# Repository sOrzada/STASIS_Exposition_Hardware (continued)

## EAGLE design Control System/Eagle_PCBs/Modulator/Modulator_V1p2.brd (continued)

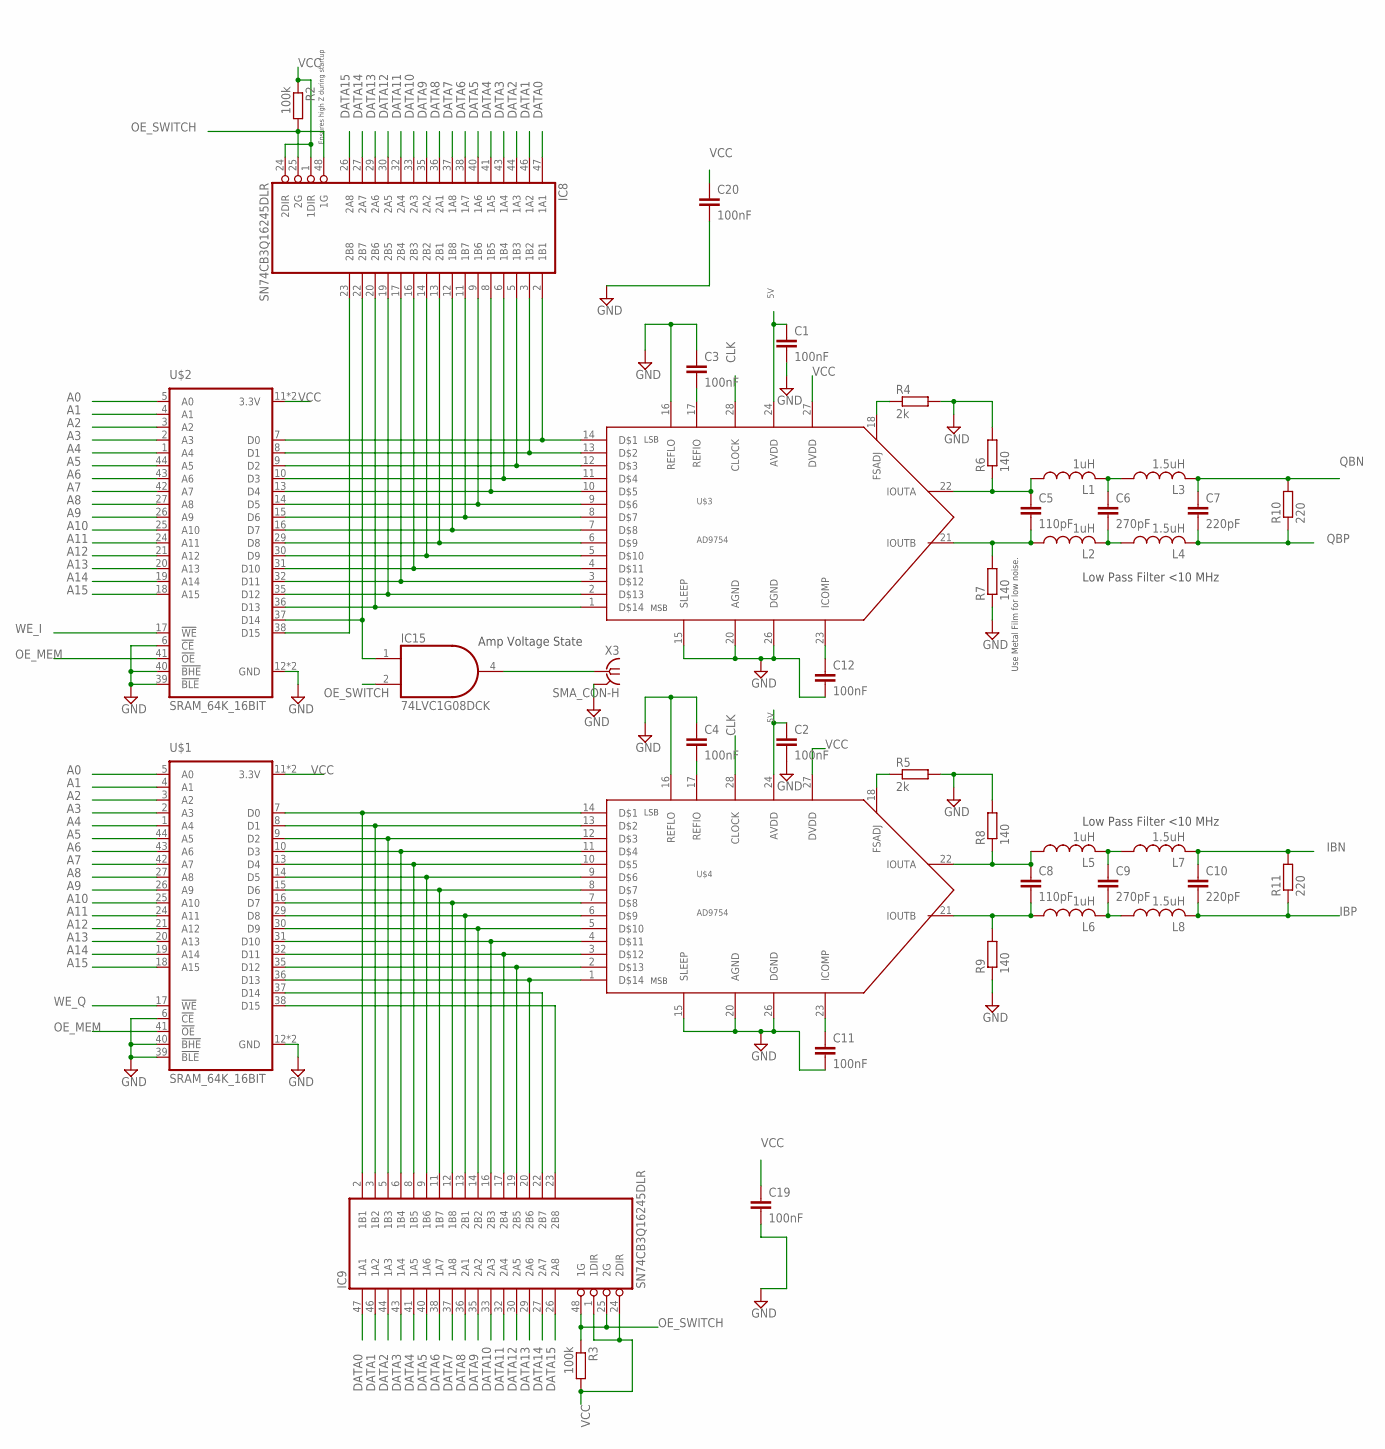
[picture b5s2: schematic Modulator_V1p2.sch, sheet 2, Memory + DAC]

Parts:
C1, C2, C3, C4, C11, C12, C19, C20: 100nF; C0603
C5, C8: 110pF; C0603
C6, C9: 270pF; C0603
C7, C10: 220pF; C0603
IC8, IC9: SN74CB3Q16245DLR; SSOP48DL
IC15: 74LVC1G08DCK; SC70-5
L1, L2, L5, L6: 1uH; L2012C
L3, L4, L7, L8: 1.5uH; L2012C
R2, R3: 100k; R0603
R4, R5: 2k; R0603
R6, R7, R8, R9: 140; R0603
R10, R11: 220; R0603
U$1, U$2: SRAM_64K_16BIT; TSOPII-Z44
U$3, U$4: AD9754; TSSOP28
X3: SMA_CON-H; BU-SMA-H

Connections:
5V: C1.1, C2.1, U$3.24 (AVDD), U$4.24 (AVDD); also elsewhere on the board
A0: U$1.5 (A0), U$2.5 (A0); also elsewhere on the board
A1: U$1.4 (A1), U$2.4 (A1); also elsewhere on the board
A2: U$1.3 (A2), U$2.3 (A2); also elsewhere on the board
A3: U$1.2 (A3), U$2.2 (A3); also elsewhere on the board
A4: U$1.1 (A4), U$2.1 (A4); also elsewhere on the board
A5: U$1.44 (A5), U$2.44 (A5); also elsewhere on the board
A6: U$1.43 (A6), U$2.43 (A6); also elsewhere on the board
A7: U$1.42 (A7), U$2.42 (A7); also elsewhere on the board
A8: U$1.27 (A8), U$2.27 (A8); also elsewhere on the board
A9: U$1.26 (A9), U$2.26 (A9); also elsewhere on the board
A10: U$1.25 (A10), U$2.25 (A10); also elsewhere on the board
A11: U$1.24 (A11), U$2.24 (A11); also elsewhere on the board
A12: U$1.21 (A12), U$2.21 (A12); also elsewhere on the board
A13: U$1.20 (A13), U$2.20 (A13); also elsewhere on the board
A14: U$1.19 (A14), U$2.19 (A14); also elsewhere on the board
A15: U$1.18 (A15), U$2.18 (A15); also elsewhere on the board
CLK: U$3.28 (CLOCK), U$4.28 (CLOCK); also elsewhere on the board
DATA0: IC8.47 (1A1), IC9.47 (1A1); also elsewhere on the board
DATA1: IC8.46 (1A2), IC9.46 (1A2); also elsewhere on the board
DATA2: IC8.44 (1A3), IC9.44 (1A3); also elsewhere on the board
DATA3: IC8.43 (1A4), IC9.43 (1A4); also elsewhere on the board
DATA4: IC8.41 (1A5), IC9.41 (1A5); also elsewhere on the board
DATA5: IC8.40 (1A6), IC9.40 (1A6); also elsewhere on the board
DATA6: IC8.38 (1A7), IC9.38 (1A7); also elsewhere on the board
DATA7: IC8.37 (1A8), IC9.37 (1A8); also elsewhere on the board
DATA8: IC8.36 (2A1), IC9.36 (2A1); also elsewhere on the board
DATA9: IC8.35 (2A2), IC9.35 (2A2); also elsewhere on the board
DATA10: IC8.33 (2A3), IC9.33 (2A3); also elsewhere on the board
DATA11: IC8.32 (2A4), IC9.32 (2A4); also elsewhere on the board
DATA12: IC8.30 (2A5), IC9.30 (2A5); also elsewhere on the board
DATA13: IC8.29 (2A6), IC9.29 (2A6); also elsewhere on the board
DATA14: IC8.27 (2A7), IC9.27 (2A7); also elsewhere on the board
DATA15: IC8.26 (2A8), IC9.26 (2A8); also elsewhere on the board
DI0: IC8.2 (1B1), U$2.7 (D0), U$3.14
DI1: IC8.3 (1B2), U$2.8 (D1), U$3.13
DI2: IC8.5 (1B3), U$2.9 (D2), U$3.12
DI3: IC8.6 (1B4), U$2.10 (D3), U$3.11
DI4: IC8.8 (1B5), U$2.13 (D4), U$3.10
DI5: IC8.9 (1B6), U$2.14 (D5), U$3.9
DI6: IC8.11 (1B7), U$2.15 (D6), U$3.8
DI7: IC8.12 (1B8), U$2.16 (D7), U$3.7
DI8: IC8.13 (2B1), U$2.29 (D8), U$3.6
DI9: IC8.14 (2B2), U$2.30 (D9), U$3.5
DI10: IC8.16 (2B3), U$2.31 (D10), U$3.4
DI11: IC8.17 (2B4), U$2.32 (D11), U$3.3
DI12: IC8.19 (2B5), U$2.35 (D12), U$3.2
DI13: IC8.20 (2B6), U$2.36 (D13), U$3.1
DQ0: IC9.2 (1B1), U$1.7 (D0), U$4.14
DQ1: IC9.3 (1B2), U$1.8 (D1), U$4.13
DQ2: IC9.5 (1B3), U$1.9 (D2), U$4.12
DQ3: IC9.6 (1B4), U$1.10 (D3), U$4.11
DQ4: IC9.8 (1B5), U$1.13 (D4), U$4.10
DQ5: IC9.9 (1B6), U$1.14 (D5), U$4.9
DQ6: IC9.11 (1B7), U$1.15 (D6), U$4.8
DQ7: IC9.12 (1B8), U$1.16 (D7), U$4.7
DQ8: IC9.13 (2B1), U$1.29 (D8), U$4.6
DQ9: IC9.14 (2B2), U$1.30 (D9), U$4.5
DQ10: IC9.16 (2B3), U$1.31 (D10), U$4.4
DQ11: IC9.17 (2B4), U$1.32 (D11), U$4.3
DQ12: IC9.19 (2B5), U$1.35 (D12), U$4.2
DQ13: IC9.20 (2B6), U$1.36 (D13), U$4.1
GND: C1.2, C2.2, C3.1, C4.1, C11.2, C12.2, C19.2, C20.2, IC8.4 (GND), IC8.10 (GND), IC8.15 (GND), IC8.21 (GND), IC8.28 (GND), IC8.34 (GND), IC8.39 (GND), IC8.45 (GND), IC9.4 (GND), IC9.10 (GND), IC9.15 (GND), IC9.21 (GND), IC9.28 (GND), IC9.34 (GND), IC9.39 (GND), IC9.45 (GND), IC15.3 (GND), R4.2, R5.2, R6.2, R7.1, R8.2, R9.1, U$1.6 (!CE), U$1.12 (GND), U$1.34 (GND), U$1.39 (!BLE), U$1.40 (!BHE), U$2.6 (!CE), U$2.12 (GND), U$2.34 (GND), U$2.39 (!BLE), U$2.40 (!BHE), U$3.15 (SLEEP), U$3.16 (REFLO), U$3.20 (AGND), U$3.26 (DGND), U$4.15 (SLEEP), U$4.16 (REFLO), U$4.20 (AGND), U$4.26 (DGND), X3.2 (GND), X3.3 (GND), X3.4 (GND), X3.5 (GND); also elsewhere on the board
IBN: C10.1, L7.2, R11.2; also elsewhere on the board
IBP: C10.2, L8.2, R11.1; also elsewhere on the board
unnamed: IC8.22 (2B7), IC15.1 (I0), U$2.37 (D14)
unnamed: IC8.23 (2B8), U$2.38 (D15)
unnamed: IC9.22 (2B7), U$1.37 (D14)
unnamed: IC9.23 (2B8), U$1.38 (D15)
unnamed: R5.1, U$4.18 (FSADJ)
unnamed: IC15.4 (O), X3.1
unnamed: C6.1, L1.2, L3.1
unnamed: R4.1, U$3.18 (FSADJ)
unnamed: C6.2, L2.2, L4.1
unnamed: C3.2, U$3.17 (REFIO)
unnamed: C4.2, U$4.17 (REFIO)
unnamed: C8.1, L5.1, R8.1, U$4.22 (IOUTA)
unnamed: C8.2, L6.1, R9.2, U$4.21 (IOUTB)
unnamed: C5.1, L1.1, R6.1, U$3.22 (IOUTA)
unnamed: C9.1, L5.2, L7.1
unnamed: C5.2, L2.1, R7.2, U$3.21 (IOUTB)
unnamed: C11.1, U$4.23 (ICOMP)
unnamed: C9.2, L6.2, L8.1
unnamed: C12.1, U$3.23 (ICOMP)
OE_MEM: U$1.41 (!OE), U$2.41 (!OE); also elsewhere on the board
OE_SWITCH: IC8.25 (2G), IC8.48 (1G), IC9.25 (2G), IC9.48 (1G), IC15.2 (I1), R2.2, R3.1; also elsewhere on the board
QBN: C7.1, L3.2, R10.2; also elsewhere on the board
QBP: C7.2, L4.2, R10.1; also elsewhere on the board
VCC: C19.1, C20.1, IC8.1 (1DIR), IC8.7 (VCC), IC8.18 (VCC), IC8.24 (2DIR), IC8.31 (VCC), IC8.42 (VCC), IC9.1 (1DIR), IC9.7 (VCC), IC9.18 (VCC), IC9.24 (2DIR), IC9.31 (VCC), IC9.42 (VCC), IC15.5 (VCC), R2.1, R3.2, U$1.11 (3.3V), U$1.33 (3.3V), U$2.11 (3.3V), U$2.33 (3.3V), U$3.27 (DVDD), U$4.27 (DVDD); also elsewhere on the board
WE_I: U$2.17 (!WE); also elsewhere on the board
WE_Q: U$1.17 (!WE); also elsewhere on the board

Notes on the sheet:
Ensures high Z during startup
Use Metal Film for low noise.
Low Pass Filter <10 MHz
Amp Voltage State

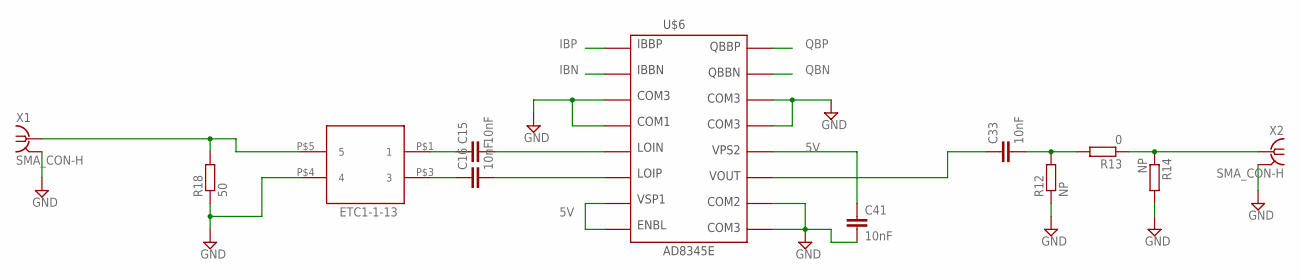
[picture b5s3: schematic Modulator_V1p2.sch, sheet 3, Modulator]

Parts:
C15, C16, C33: 10nF; C0402
C41: 10nF; C0603
R12, R14: NP; R0805
R13: 0; R0805
R18: 50; R0603
U$6: AD8345E; TSSOP16EXP
U$12: ETC1-1-13
X1, X2: SMA_CON-H; BU-SMA-H

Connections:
5V: C41.1, U$6.7, U$6.8, U$6.12; also elsewhere on the board
GND: C41.2, R12.1, R14.2, R18.1, U$6.3, U$6.4, U$6.9, U$6.10, U$6.13, U$6.14, U$6.EXP, U$12.P$4 (4), X1.2 (GND), X1.3 (GND), X1.4 (GND), X1.5 (GND), X2.2 (GND), X2.3 (GND), X2.4 (GND), X2.5 (GND); also elsewhere on the board
IBN: U$6.2; also elsewhere on the board
IBP: U$6.1; also elsewhere on the board
unnamed: C33.1, U$6.11
unnamed: C15.1, U$12.P$1 (1)
unnamed: C16.1, U$12.P$3 (3)
unnamed: R18.2, U$12.P$5 (5), X1.1
unnamed: C15.2, U$6.5
unnamed: C16.2, U$6.6
unnamed: R13.1, R14.1, X2.1
unnamed: C33.2, R12.2, R13.2
QBN: U$6.15; also elsewhere on the board
QBP: U$6.16; also elsewhere on the board

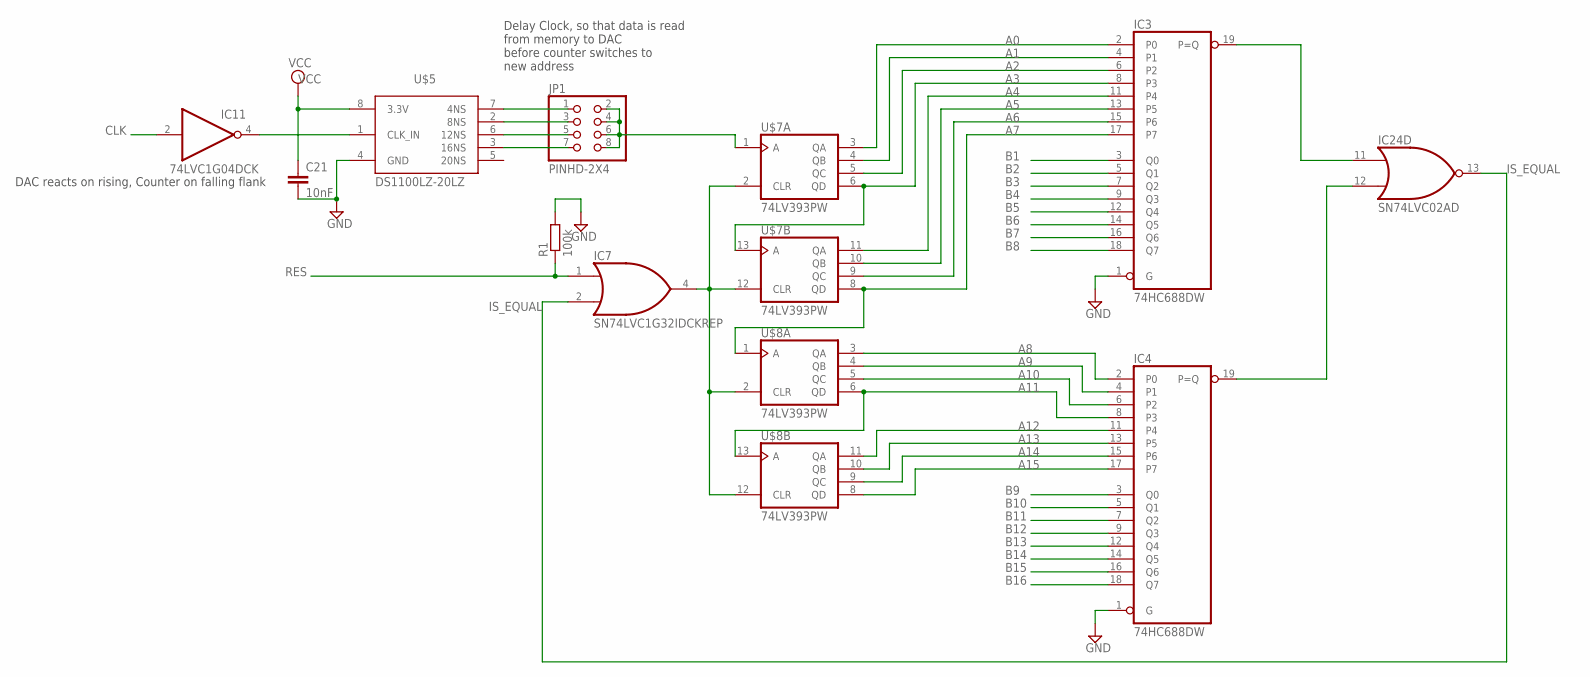
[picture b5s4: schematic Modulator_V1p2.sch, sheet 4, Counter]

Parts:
C21: 10nF; C0603
IC3, IC4: 74HC688DW; SO20W
IC7: SN74LVC1G32IDCKREP; SC70-5
IC11: 74LVC1G04DCK; SC70-5
IC24: SN74LVC02AD; SO14
JP1: PINHD-2X4; 2X04
R1: 100k; R0603
U$5: DS1100LZ-20LZ; SO-08
U$7, U$8: 74LV393PW; TSSOP14

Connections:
A0: IC3.2 (P0), U$7.3 (QA); also elsewhere on the board
A1: IC3.4 (P1), U$7.4 (QB); also elsewhere on the board
A2: IC3.6 (P2), U$7.5 (QC); also elsewhere on the board
A3: IC3.8 (P3), U$7.6 (QD), U$7.13 (A); also elsewhere on the board
A4: IC3.11 (P4), U$7.11 (QA); also elsewhere on the board
A5: IC3.13 (P5), U$7.10 (QB); also elsewhere on the board
A6: IC3.15 (P6), U$7.9 (QC); also elsewhere on the board
A7: IC3.17 (P7), U$7.8 (QD), U$8.1 (A); also elsewhere on the board
A8: IC4.2 (P0), U$8.3 (QA); also elsewhere on the board
A9: IC4.4 (P1), U$8.4 (QB); also elsewhere on the board
A10: IC4.6 (P2), U$8.5 (QC); also elsewhere on the board
A11: IC4.8 (P3), U$8.6 (QD), U$8.13 (A); also elsewhere on the board
A12: IC4.11 (P4), U$8.11 (QA); also elsewhere on the board
A13: IC4.13 (P5), U$8.10 (QB); also elsewhere on the board
A14: IC4.15 (P6), U$8.9 (QC); also elsewhere on the board
A15: IC4.17 (P7), U$8.8 (QD); also elsewhere on the board
B1: IC3.3 (Q0); also elsewhere on the board
B2: IC3.5 (Q1); also elsewhere on the board
B3: IC3.7 (Q2); also elsewhere on the board
B4: IC3.9 (Q3); also elsewhere on the board
B5: IC3.12 (Q4); also elsewhere on the board
B6: IC3.14 (Q5); also elsewhere on the board
B7: IC3.16 (Q6); also elsewhere on the board
B8: IC3.18 (Q7); also elsewhere on the board
B9: IC4.3 (Q0); also elsewhere on the board
B10: IC4.5 (Q1); also elsewhere on the board
B11: IC4.7 (Q2); also elsewhere on the board
B12: IC4.9 (Q3); also elsewhere on the board
B13: IC4.12 (Q4); also elsewhere on the board
B14: IC4.14 (Q5); also elsewhere on the board
B15: IC4.16 (Q6); also elsewhere on the board
B16: IC4.18 (Q7); also elsewhere on the board
CLK: IC11.2 (I); also elsewhere on the board
CLR: IC7.4 (O), U$7.2 (CLR), U$7.12 (CLR), U$8.2 (CLR), U$8.12 (CLR)
GND: C21.2, IC3.1 (G), IC3.10 (GND), IC4.1 (G), IC4.10 (GND), IC7.3 (GND), IC11.3 (GND), IC24.7 (GND), R1.2, U$5.4 (GND), U$7.7 (GND), U$8.7 (GND); also elsewhere on the board
IS_EQUAL: IC7.2 (I1), IC24.13 (O)
unnamed: IC3.19 (P=Q), IC24.11 (I0)
unnamed: IC4.19 (P=Q), IC24.12 (I1)
unnamed: JP1.2, JP1.4, JP1.6, JP1.8, U$7.1 (A)
unnamed: IC11.4 (O), U$5.1 (CLK_IN)
unnamed: JP1.1, U$5.7 (4NS)
unnamed: JP1.3, U$5.2 (8NS)
unnamed: JP1.5, U$5.6 (12NS)
unnamed: JP1.7, U$5.3 (16NS)
RES: IC7.1 (I0), R1.1; also elsewhere on the board
VCC: C21.1, IC3.20 (VCC), IC4.20 (VCC), IC7.5 (VCC), IC11.5 (VCC), IC24.14 (VCC), U$5.8 (3.3V), U$7.14 (VCC), U$8.14 (VCC); also elsewhere on the board

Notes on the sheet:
Delay Clock, so that data is read from memory to DAC before counter switches to new address
DAC reacts on rising, Counter on falling flank

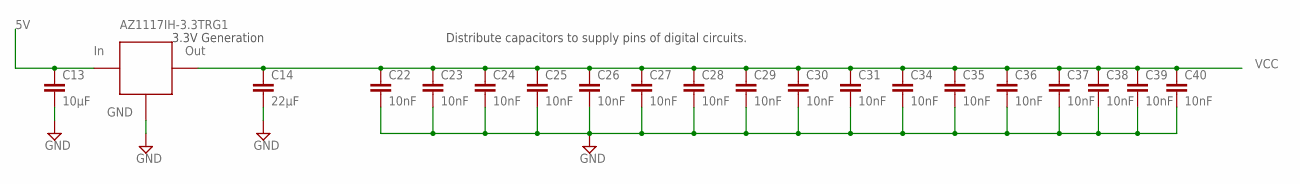
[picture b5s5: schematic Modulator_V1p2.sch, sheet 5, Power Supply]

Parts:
C13: 10µF; C1206
C14: 22µF; C1206
C22, C23, C24, C25, C26, C27, C28, C29, C30, C31, C34, C35, C36, C37, C38, C39, C40: 10nF; C0603
U$9: AZ1117IH-3.3TRG1; SOT223

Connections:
5V: C13.1, U$9.3 (IN); also elsewhere on the board
GND: C13.2, C14.2, C22.2, C23.2, C24.2, C25.2, C26.2, C27.2, C28.2, C29.2, C30.2, C31.2, C34.2, C35.2, C36.2, C37.2, C38.2, C39.2, C40.2, U$9.1 (GND); also elsewhere on the board
VCC: C14.1, C22.1, C23.1, C24.1, C25.1, C26.1, C27.1, C28.1, C29.1, C30.1, C31.1, C34.1, C35.1, C36.1, C37.1, C38.1, C39.1, C40.1, U$9.2 (OUT), U$9.4 (OUT); also elsewhere on the board

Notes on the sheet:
3.3V Generation
Distribute capacitors to supply pins of digital circuits.

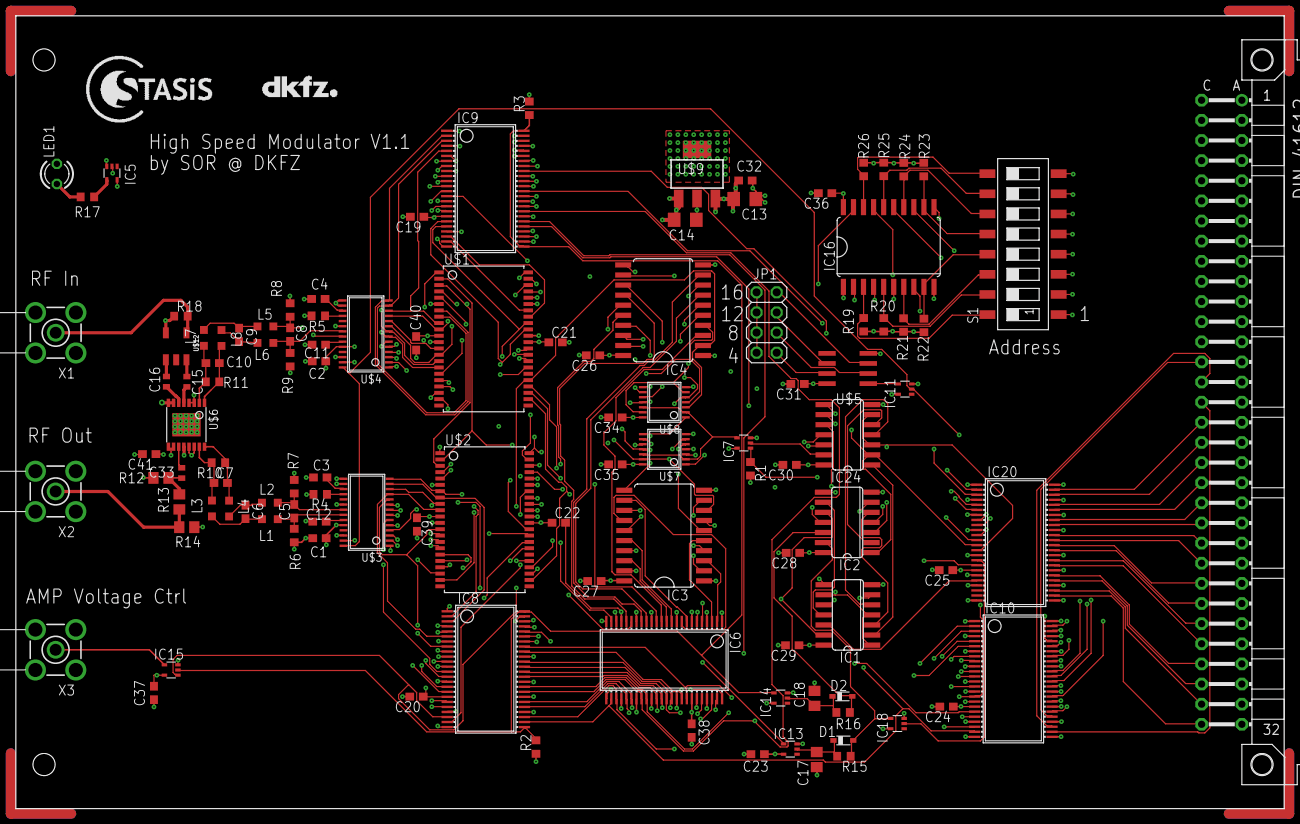
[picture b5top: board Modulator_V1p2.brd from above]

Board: 6 copper layers, 160.0 x 100.0 mm, 114 parts (0 on the bottom side), 195 nets.

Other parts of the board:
U$10: LOGO_DKFZ
U$11: LOGO_STASIS

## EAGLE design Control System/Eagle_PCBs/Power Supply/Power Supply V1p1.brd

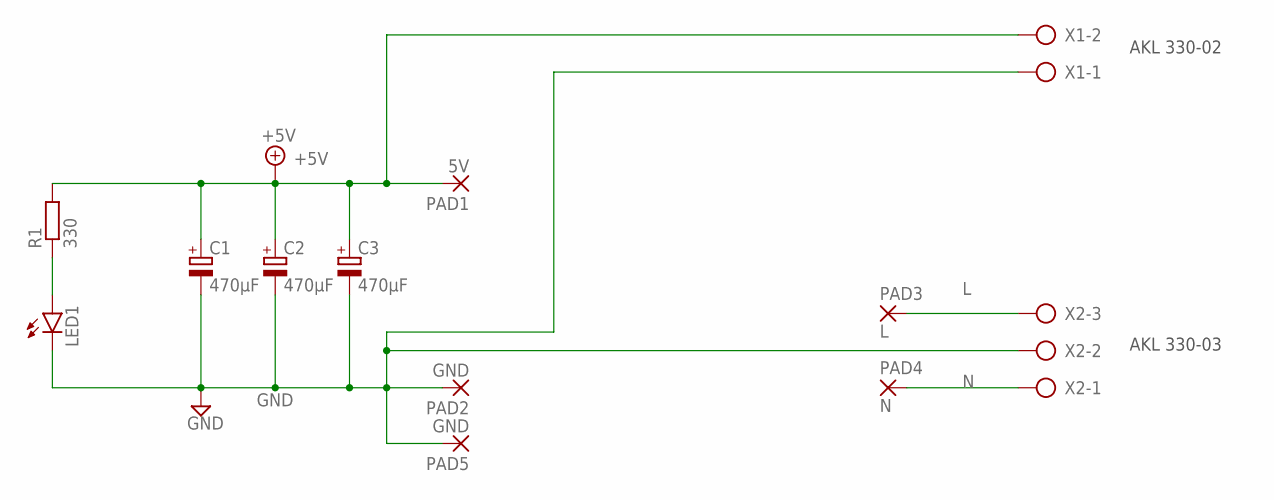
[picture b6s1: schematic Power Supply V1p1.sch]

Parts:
C1, C2, C3: 470µF; E5-10,5
LED1: LED5MM
PAD1: 5V; SMD2,54-5,08
PAD2, PAD5: GND; SMD2,54-5,08
PAD3: L; SMD2,54-5,08
PAD4: N; SMD2,54-5,08
R1: 330; R1206
X1: AK500/2-H
X2: AK500/3-H

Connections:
+5V: C1.+, C2.+, C3.+, PAD1.1, R1.2, X1.2
GND: C1.-, C2.-, C3.-, LED1.K (C), PAD2.1, PAD5.1, X1.1, X2.2
L: PAD3.1, X2.3
N: PAD4.1, X2.1
unnamed: LED1.A, R1.1

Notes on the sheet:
AKL 330-02
AKL 330-03

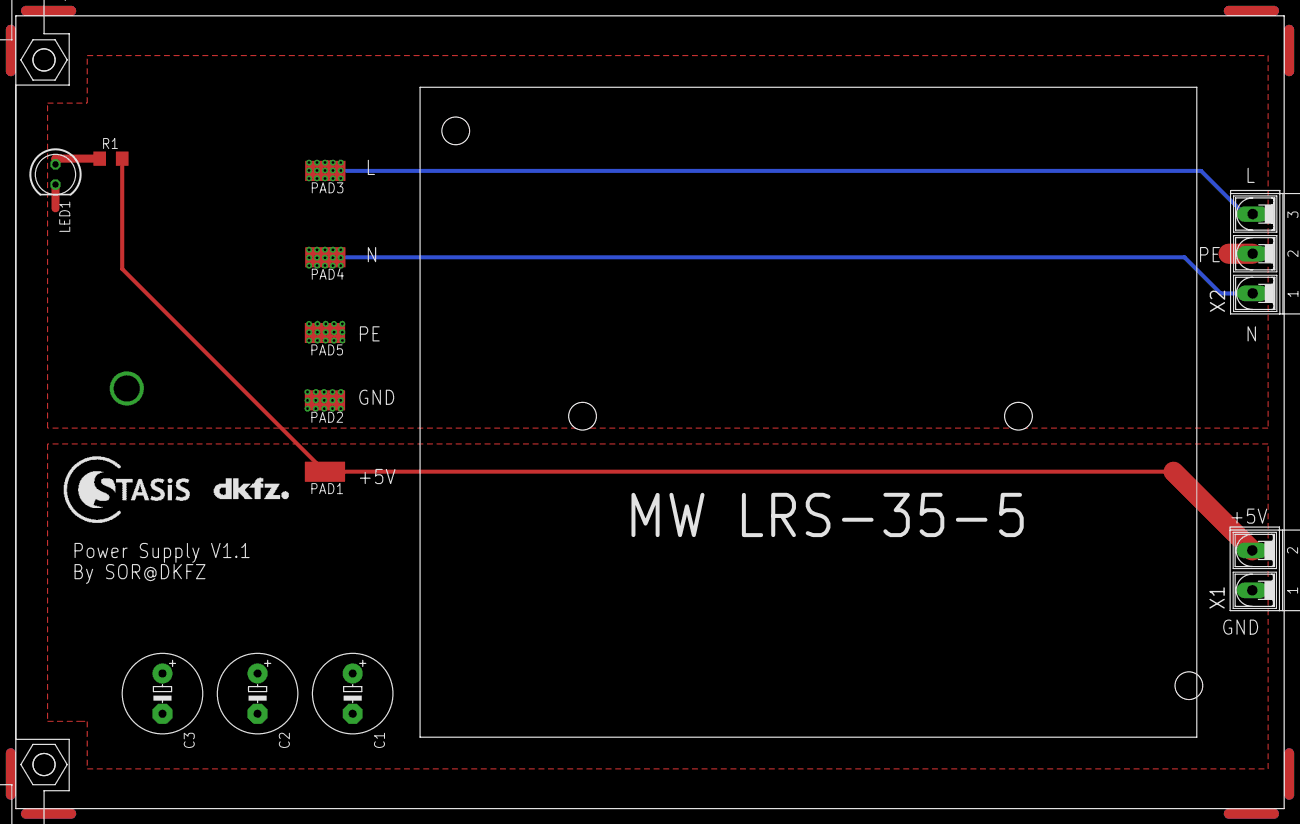
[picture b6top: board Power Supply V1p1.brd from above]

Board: 2 copper layers, 160.0 x 100.0 mm, 15 parts (0 on the bottom side), 5 nets.

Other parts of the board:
U$1: EK-FP
U$2: LOGO_STASIS
U$3: LOGO_DKFZ
